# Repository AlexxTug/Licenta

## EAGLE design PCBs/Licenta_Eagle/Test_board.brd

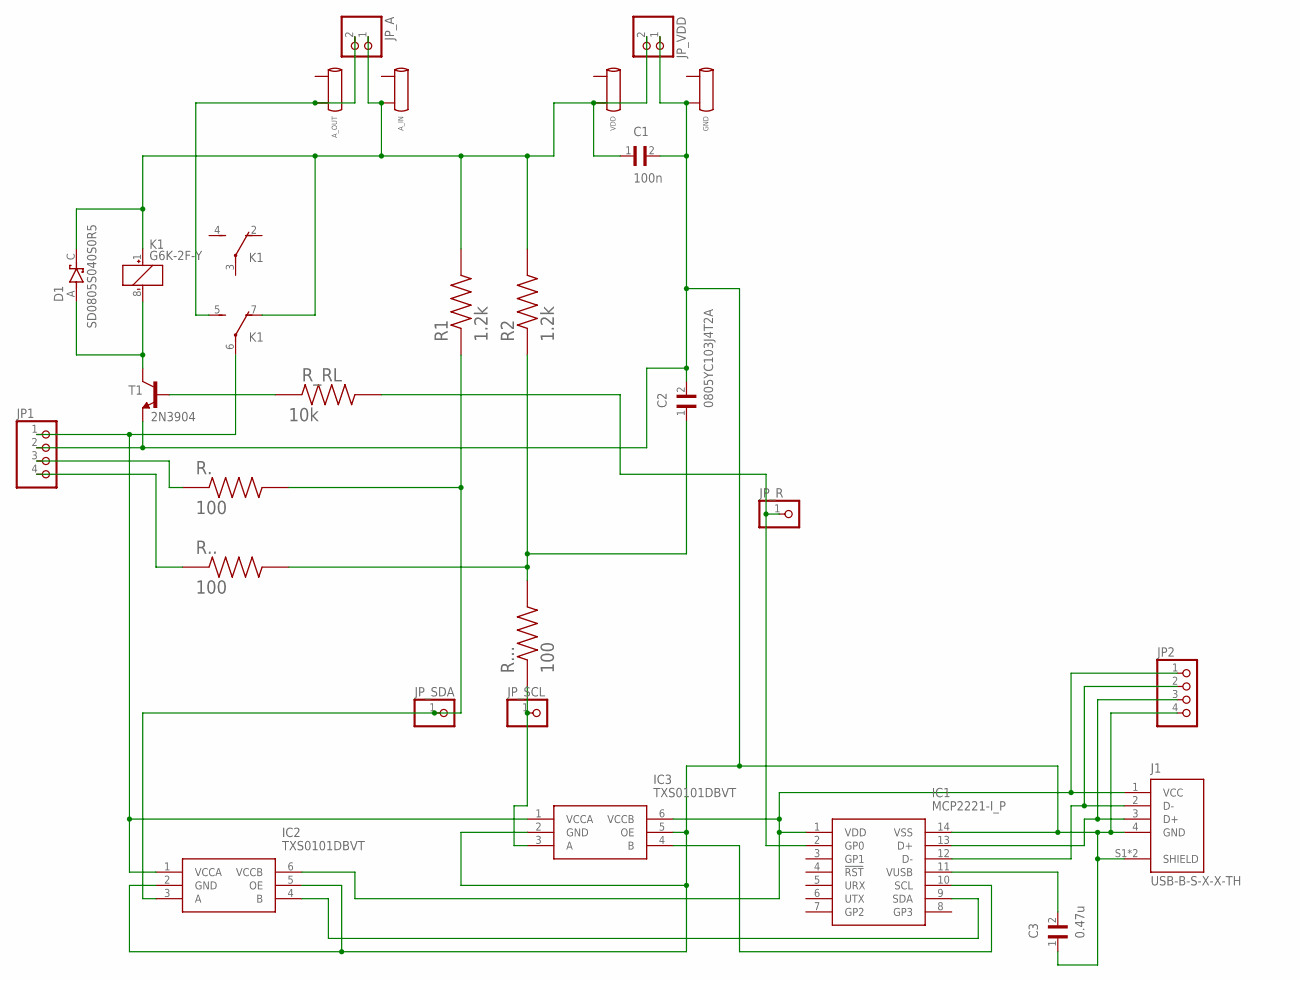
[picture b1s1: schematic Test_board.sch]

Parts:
A_IN: FY_TESTSOCKET
A_OUT: FY_TESTSOCKET
C1: 100n; CAPC2012X94N
C2: 0805YC103J4T2A; CAPC2012X94N
C3: 0.47u; CAPC2012X94N
D1: SD0805S040S0R5; DIOSC130X200X100-2N
GND: FY_TESTSOCKET
IC1: MCP2221-I_P; DIP781W56P254L1918H533Q14N
IC2, IC3: TXS0101DBVT; SOT95P280X145-6N
J1: USB-B-S-X-X-TH; SAMTEC_USB-B-S-X-X-TH
JP1, JP2: PINHD-1X4; 1X04
JP_A: PINHD-1X2; 1X02
JP_R: PINHD-1X1; 1X01
JP_SCL: PINHD-1X1; 1X01
JP_SDA: PINHD-1X1; 1X01
JP_VDD: PINHD-1X2; 1X02
K1: G6K-2F-Y
R1, R2: 1.2k; RESC2012X60N
R., R.., R...: 100; RESC2012X60N
R_RL: 10k; RESC2012X60N
T1: 2N3904; TO92
VDD: FY_TESTSOCKET

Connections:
unnamed: D1.A, K1.8 (-), T1.1 (C)
unnamed: C1.2, C2.2, C3.1, GND.P$2, IC1.14 (VSS), IC2.2 (GND), IC2.5 (OE), IC3.2 (GND), IC3.5 (OE), J1.4 (GND), J1.S1 (SHIELD), J1.S2 (SHIELD), JP1.2, JP2.4, JP_VDD.1, T1.3 (E)
unnamed: A_OUT.P$2, JP_A.2, K1.5 (S)
unnamed: C3.2, IC1.11 (VUSB)
unnamed: C2.1, R2.1, R...2, R....2
unnamed: IC2.3 (A), JP_SDA.1, R1.1, R..2
unnamed: IC3.3 (A), JP_SCL.1, R....1
unnamed: JP1.3, R..1
unnamed: JP1.4, R...1
unnamed: IC2.1 (VCCA), IC3.1 (VCCA), JP1.1, K1.6
unnamed: IC1.9 (SDA), IC2.4 (B)
unnamed: IC1.10 (SCL), IC3.4 (B)
unnamed: IC1.1 (VDD), IC2.6 (VCCB), IC3.6 (VCCB), J1.1 (VCC), JP2.1
unnamed: R_RL.1, T1.2 (B)
unnamed: A_IN.P$2, C1.1, D1.C (K), JP_A.1, JP_VDD.2, K1.1 (+), K1.7 (O), R1.2, R2.2, VDD.P$2
unnamed: IC1.13 (D+), J1.3 (D+), JP2.3
unnamed: IC1.12 (D-), J1.2 (D-), JP2.2
unnamed: IC1.2 (GP0), JP_R.1, R_RL.2

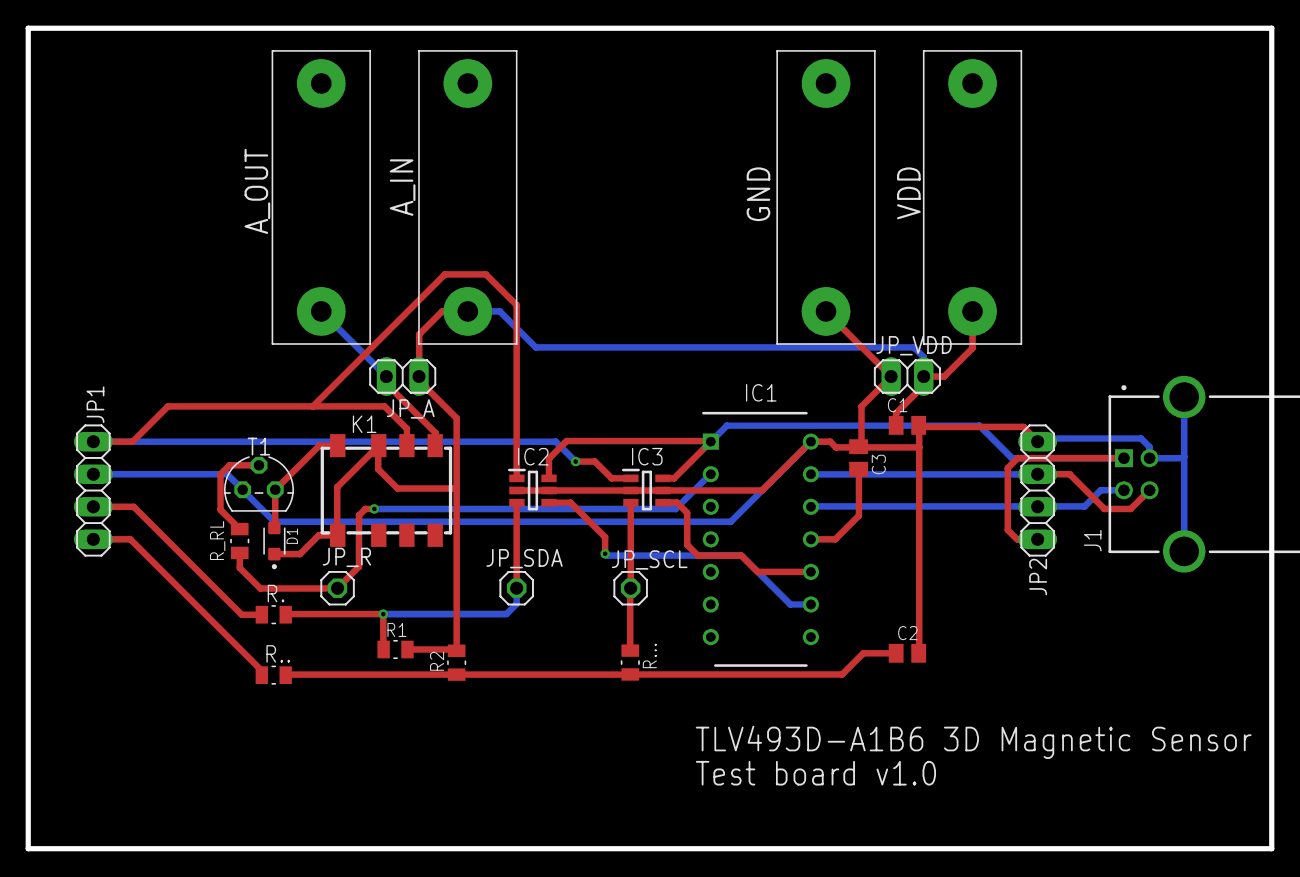
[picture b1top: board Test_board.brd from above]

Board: 2 copper layers, 97.0 x 64.0 mm, 27 parts (0 on the bottom side), 18 nets.

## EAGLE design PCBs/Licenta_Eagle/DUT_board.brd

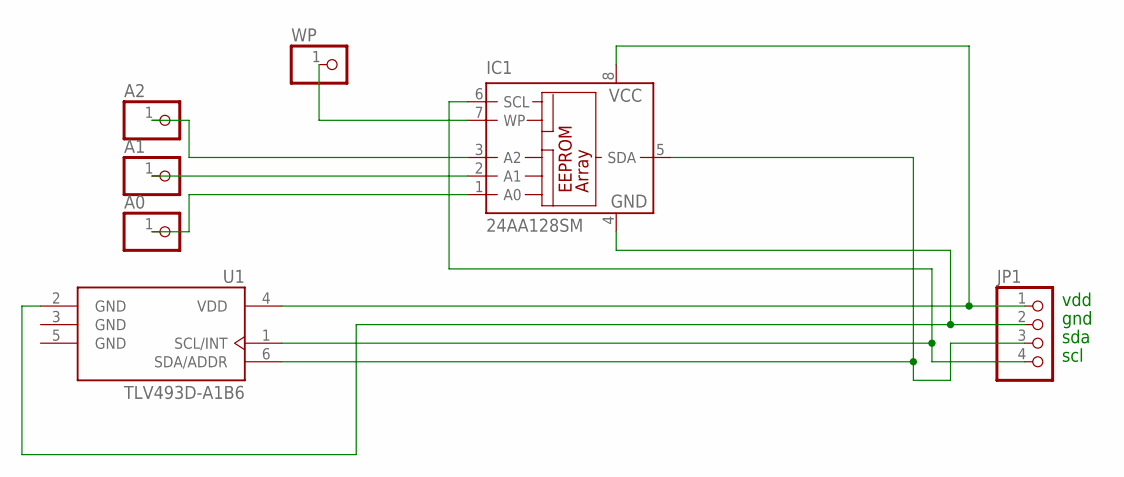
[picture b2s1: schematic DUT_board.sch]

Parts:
A0, A1, A2: PINHD-1X1; 1X01
IC1: 24AA128SM; SO-08M
JP1: PINHD-1X4; 1X04
U1: TLV493D-A1B6; SOP95P250X110-6N-1-V1
WP: PINHD-1X1; 1X01

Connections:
GND: U1.3 (GND), U1.5 (GND)
unnamed: IC1.8 (VCC), JP1.1, U1.4 (VDD)
unnamed: IC1.4 (GND), JP1.2, U1.2 (GND)
unnamed: IC1.6 (SCL), JP1.4, U1.1 (SCL/INT)
unnamed: IC1.5 (SDA), JP1.3, U1.6 (SDA/ADDR)
unnamed: A2.1, IC1.3 (A2)
unnamed: A1.1, IC1.2 (A1)
unnamed: A0.1, IC1.1 (A0)
unnamed: IC1.7 (WP), WP.1

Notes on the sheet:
vdd
gnd
sda
scl

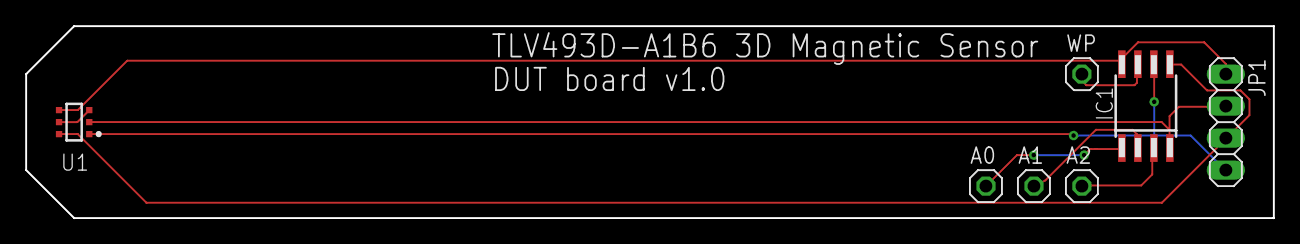
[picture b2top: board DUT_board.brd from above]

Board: 2 copper layers, 99.1 x 15.2 mm, 7 parts (0 on the bottom side), 9 nets.
